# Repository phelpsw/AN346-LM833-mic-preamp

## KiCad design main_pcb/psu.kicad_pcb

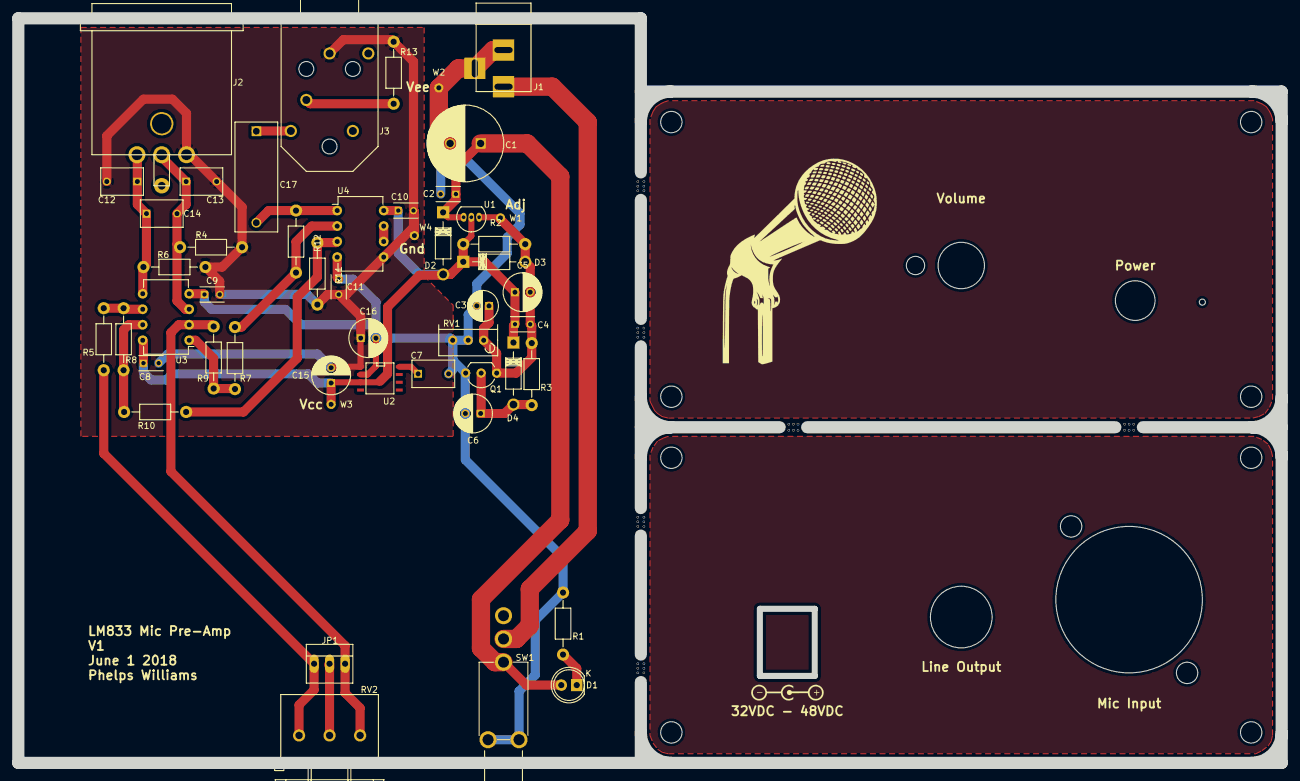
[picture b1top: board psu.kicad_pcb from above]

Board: 2 copper layers, 207.0 x 122.0 mm, 50 parts (0 on the bottom side), 23 nets.

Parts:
C1: 470uF; C_Radial_D12.5_L25_P5
C2, C4, C8, C9, C10, C11: 0.1uF; C_Rect_L4_W2.5_P2.5
C3: 10uF/63V; C_Radial_D5_L11_P2
C5, C6, C15, C16: 25uF; C_Radial_D6.3_L11.2_P2.5
C7: 1uF; C_Rect_L7_W4.5_P5
C12, C13: 470pF; C_Rect_L7_W4.5_P5
C14: 200pF; C_Rect_L7_W4.5_P5
C17: 1uF; C_Rect_L18_W7_P15
D1: LED; LED-5MM
D2, D3, D4: 1N4002; Diode_DO-41_SOD81_Horizontal_RM10
J1: BARREL_JACK
J2: XLR3; XLR3MC
J3: JACK_TRS_3PINS; RN112APC
JP1: JUMPER3; PINHEAD1-3
Q1: PN2907; TO-92_Inline_Wide
R1: R; Resistor_Horizontal_RM10mm
R2: 270; Resistor_Horizontal_RM10mm
R3: 51k; Resistor_Horizontal_RM10mm
R4, R6: 1k; Resistor_Horizontal_RM10mm
R5: 150; Resistor_Horizontal_RM10mm
R7, R8, R9, R10: 10k; Resistor_Horizontal_RM10mm
R11, R12: 20k; Resistor_Horizontal_RM10mm
R13: 1M; Resistor_Horizontal_RM10mm
RV1: 10k; Potentiometer_Bourns_3296W_3-8Zoll_Inline_ScrewUp
RV2: 20k; RK163
SW1: M2012S2A2W40
U1: LM317L-N; TO-92_Inline_Narrow_Oval
U2: TLE2426-SOIC; SOIC-8-N
U3, U4: LM833; DIP-8_W7.62mm
W1, W2, W3, W4: TEST_1P; Measurement_Point_Round-TH_Small

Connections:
GND: C8.2, C9.2, C10.2, C11.2, C12.2, C13.2, C15.2, C16.1, J2.1, J3.1, R4.2, R6.2, R11.2, R13.2, U2.1, U4.5, W4.1
GNDPWR: C1.2, C2.2, C3.2, C6.2, C7.2, C9.1, C11.1, C16.2, J1.2, J1.3, Q1.3, R1.2, RV1.2, RV1.3, SW1.4, SW1.5, U2.2, U3.4, U4.4, W2.1
unnamed: C1.1, C2.1, D1.2, D2.1, SW1.1, U1.3
unnamed: C3.1, C4.2, C5.2, D3.2, Q1.1, R2.2, R3.2, RV1.1, U1.1, W1.1
unnamed: C6.1, D4.2, Q1.2, R3.1
unnamed: C7.1, U2.8
unnamed: C17.2, R12.1, U4.1
unnamed: D1.1, R1.1
unnamed: J1.1, SW1.2
unnamed: J3.3, R13.1
unnamed: JP1.1, R5.2, RV2.1
unnamed: JP1.2, RV2.2
unnamed: JP1.3, R7.1, RV2.3, U3.2
unnamed: R5.1, R8.1, U3.6
unnamed: R7.2, R9.1, U3.1
unnamed: R10.1, R11.1, U4.3
unnamed: R8.2, R10.2, U3.7
unnamed: R9.2, R12.2, U4.2
unnamed: U4.6, U4.7
VCC: C4.1, C5.1, C8.1, C10.1, C15.1, D2.2, D3.1, D4.1, R2.1, U1.2, U2.3, U3.8, U4.8, W3.1
Vin+: C12.1, C14.1, J2.2, R6.1, U3.5
Vin-: C13.1, C14.2, J2.3, R4.1, U3.3
Vout: C17.1, J3.2
